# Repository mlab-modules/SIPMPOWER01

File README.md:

# SIPMPOWER01A - power module for SiPM

Batterry power module to obsolete [SIPM01A](https://github.com/mlab-modules/SIPM01) Silicon photomultiplier module.
Now is superseded by using the [STEPUPDC02](https://github.com/mlab-modules/STEPUPDC02) voltage converter.

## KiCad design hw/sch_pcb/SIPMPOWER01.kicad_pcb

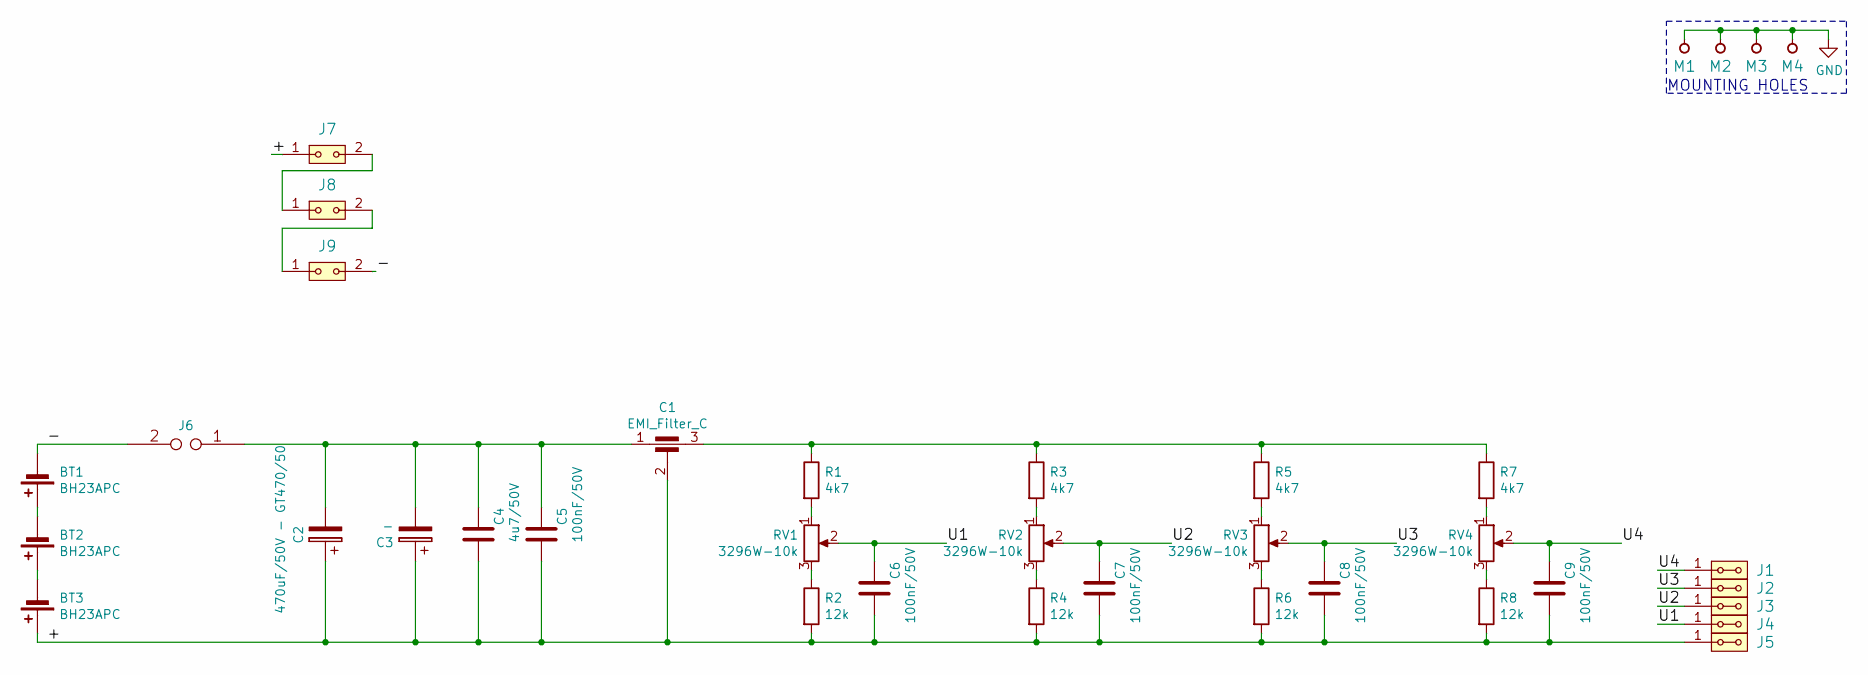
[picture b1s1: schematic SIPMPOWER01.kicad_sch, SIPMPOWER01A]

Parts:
BT1, BT2, BT3: BH23APC
C1: EMI_Filter_C; FIR_1806
C2: 470uF/50V - GT470/50; CP_Radial_D10.0mm_P5.00mm
C3: -; TantalC_SizeC_Reflow
C4: 4u7/50V; SMD-0805
C5, C6, C7, C8, C9: 100nF/50V; SMD-0805
J1, J2, J3, J4, J5: HEADER_2x01_PARALLEL; Straight_2x01
J6: JUMP2_2x1; Straight_1x02
J7, J8, J9: HEADER_2x01; Straight_1x02
M1, M2, M3, M4: HOLE; MountingHole_3mm
R1, R3, R5, R7: 4k7; SMD-0805
R2, R4, R6, R8: 12k; SMD-0805
RV1, RV2, RV3, RV4: 3296W-10k; Potentiometer_Bourns_3296W_Vertical

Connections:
/+: BT3.1 (+), C1.2, C2.1, C3.1, C4.2, C5.2, C6.2, C7.2, C8.2, C9.2, J5.1, J5.2, J7.1, R2.2, R4.2, R6.2, R8.2
/-: BT1.2 (-), J6.2, J9.2
/U1: C6.1, J4.1, J4.2, RV1.2
/U2: C7.1, J3.1, J3.2, RV2.2
/U3: C8.1, J2.1, J2.2, RV3.2
/U4: C9.1, J1.1, J1.2, RV4.2
GND: M1.1, M2.1, M3.1, M4.1
unnamed: BT1.1 (+), BT2.2 (-)
unnamed: BT2.1 (+), BT3.2 (-)
unnamed: C1.1, C2.2, C3.2, C4.1, C5.1, J6.1
unnamed: C1.3, R1.1, R3.1, R5.1, R7.1
unnamed: J7.2, J8.1
unnamed: J8.2, J9.1
unnamed: R1.2, RV1.1
unnamed: R2.1, RV1.3
unnamed: R3.2, RV2.1
unnamed: R4.1, RV2.3
unnamed: R5.2, RV3.1
unnamed: R6.1, RV3.3
unnamed: R7.2, RV4.1
unnamed: R8.1, RV4.3

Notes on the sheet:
MOUNTING HOLES

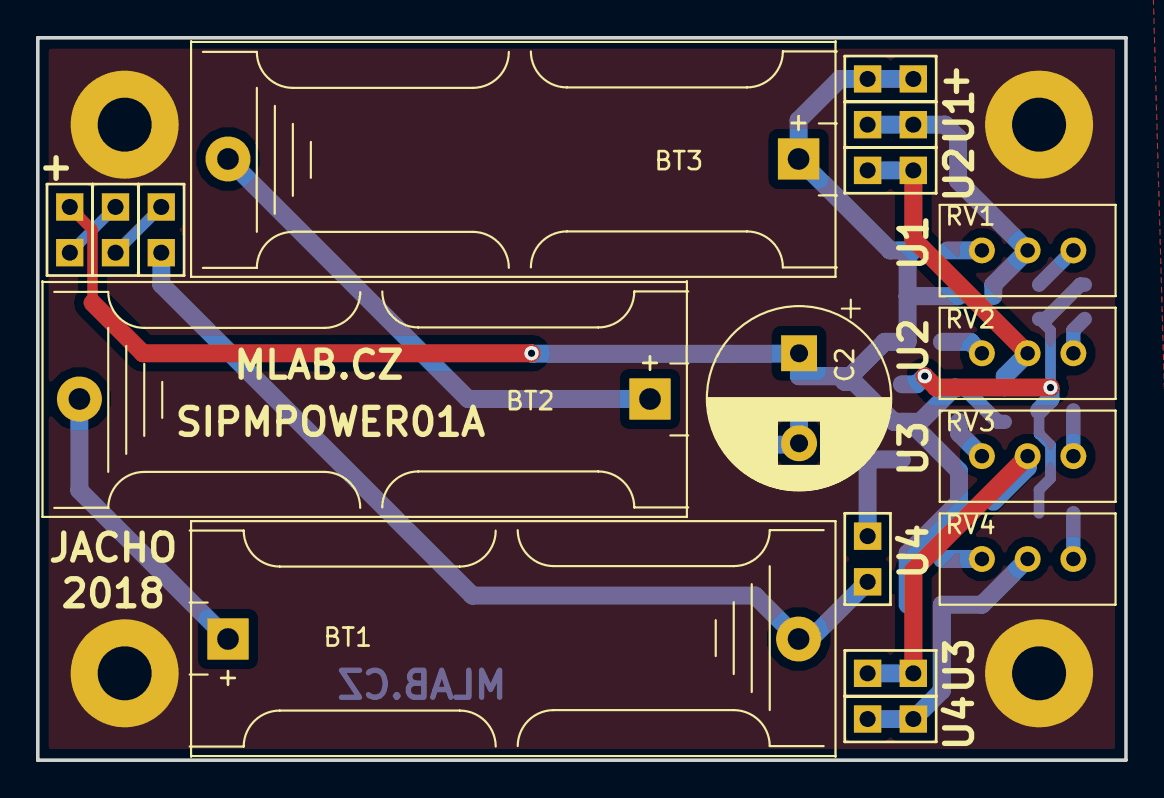
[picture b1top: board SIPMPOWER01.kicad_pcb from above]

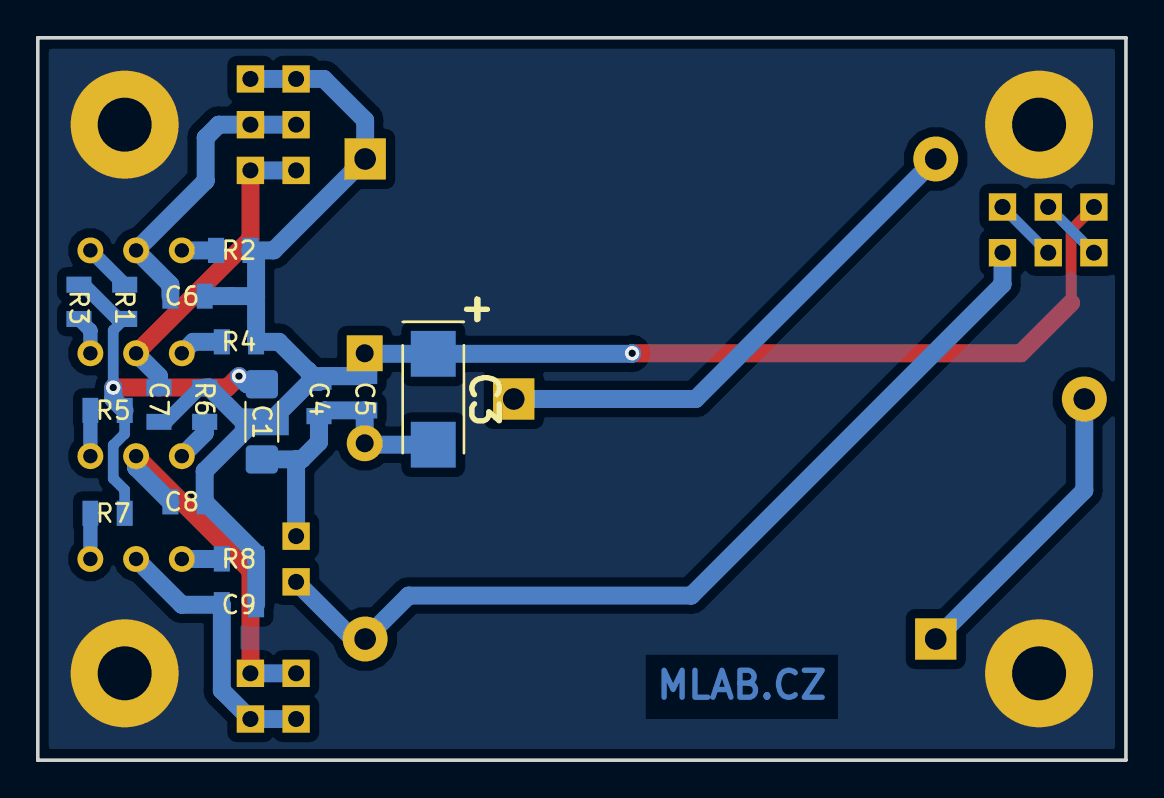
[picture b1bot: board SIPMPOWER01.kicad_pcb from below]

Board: 2 copper layers, 60.5 x 40.1 mm, 37 parts (16 on the bottom side), 21 nets.

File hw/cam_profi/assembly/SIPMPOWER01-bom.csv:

Component,Description,Part,References,Value,Footprint,Quantity Per PCB,Datasheet
1,Single-cell battery,Battery_Cell,BT1BT2BT3,BH23APC,BH23APC,3,~
2,,CP-Device,C3,-,TantalC_SizeC_Reflow,1,
3,Unpolarized capacitor,C,C5C6C7C8C9,100nF/50V,SMD-0805,5,~
4,,CP-Device,C2,470uF/50V - GT470/50,CP_Radial_D10.0mm_P5.00mm,1,
5,Unpolarized capacitor,C,C4,4u7/50V,SMD-0805,1,~
6,,EMI_Filter_C-Device,C1,EMI_Filter_C,FIR_1806,1,http://www.murata.com/~/media/webrenewal/support/library/cat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
7,2x01 2.54 mm pitch header,HEADER_2x01,J7J8J9,HEADER_2x01,Straight_1x02,3,
8,"2x01 2.54 mm pitch header, 2 pins next to each other are connected",HEADER_2x01_PARALLEL,J1J2J3J4J5,HEADER_2x01_PARALLEL,Straight_2x01,5,
9,MLAB modified doubled pinheader connector,JUMP2_2x1,J6,JUMP2_2x1,Straight_1x02,1,
10,Resistor,R,R1R3R5R7,4k7,SMD-0805,4,~
11,Resistor,R,R2R4R6R8,12k,SMD-0805,4,~
12,,R_POT-Device,RV1RV2RV3RV4,3296W-10k,Potentiometer_Bourns_3296W_Vertical,4,

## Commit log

2018-09-28 Návrh PCB
2018-09-29 Edit
2018-09-30 Modifications
2018-12-10 schema
2022-04-02 Remove unused json file.
2022-04-06 automated commit; add github actions
2023-05-25 Update metadata files
2023-05-28 Update workflow files
2023-07-05 automated commit; rename source files to new naming convence
2023-09-16 Update status
2024-07-04 Update to KiCADv7.
2024-07-04 Update project file names.
2024-07-04 Update actions products
2024-07-04 Update readme.
